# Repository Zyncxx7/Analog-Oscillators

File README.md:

# Analog-Oscillators
# Analog-Oscillators
# Analog-Oscillators

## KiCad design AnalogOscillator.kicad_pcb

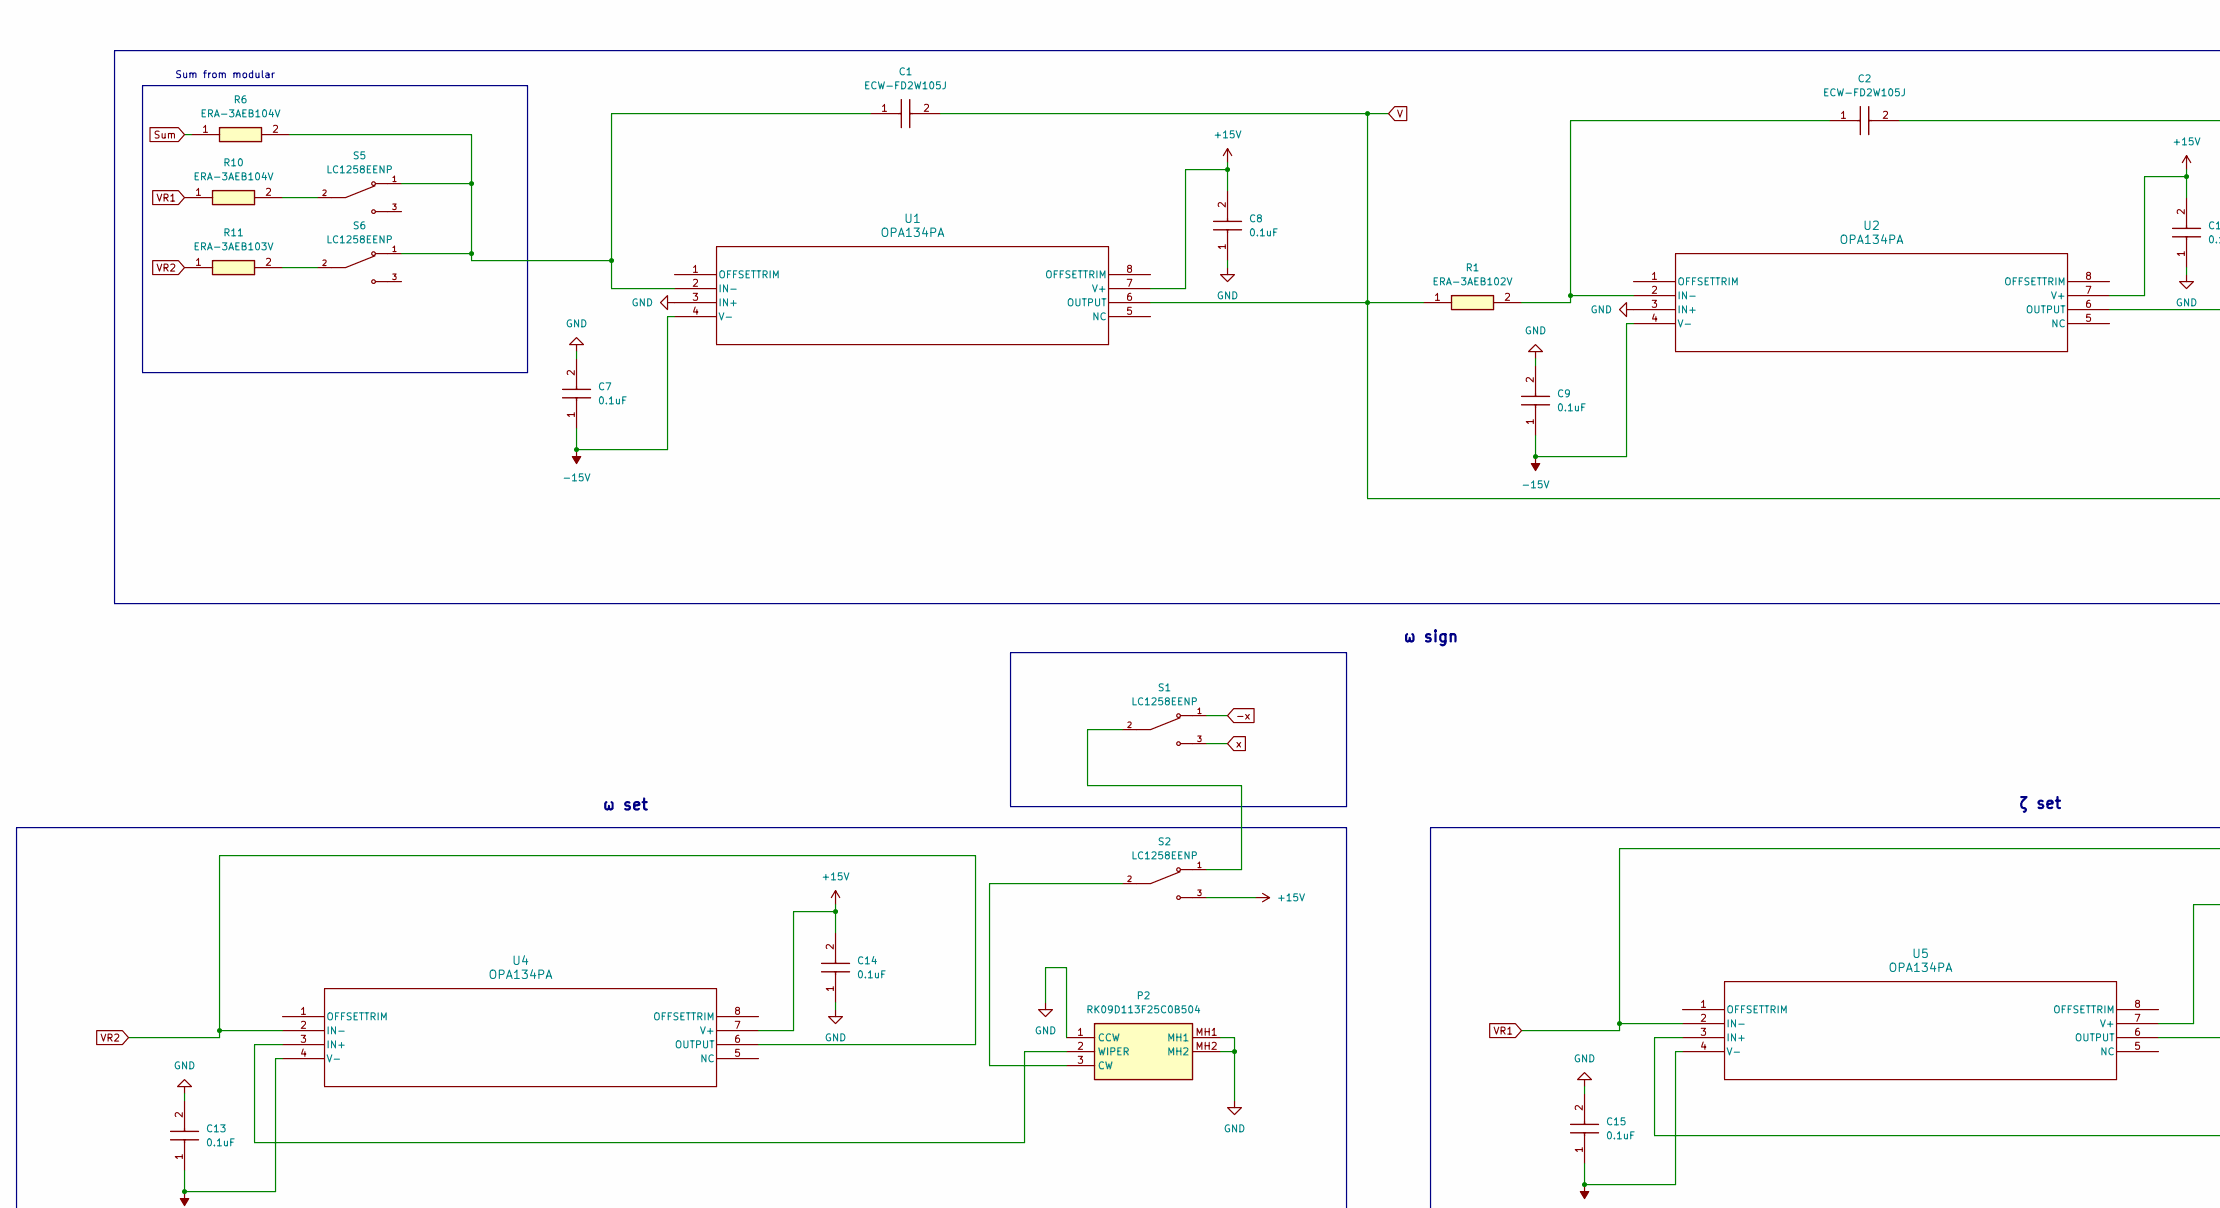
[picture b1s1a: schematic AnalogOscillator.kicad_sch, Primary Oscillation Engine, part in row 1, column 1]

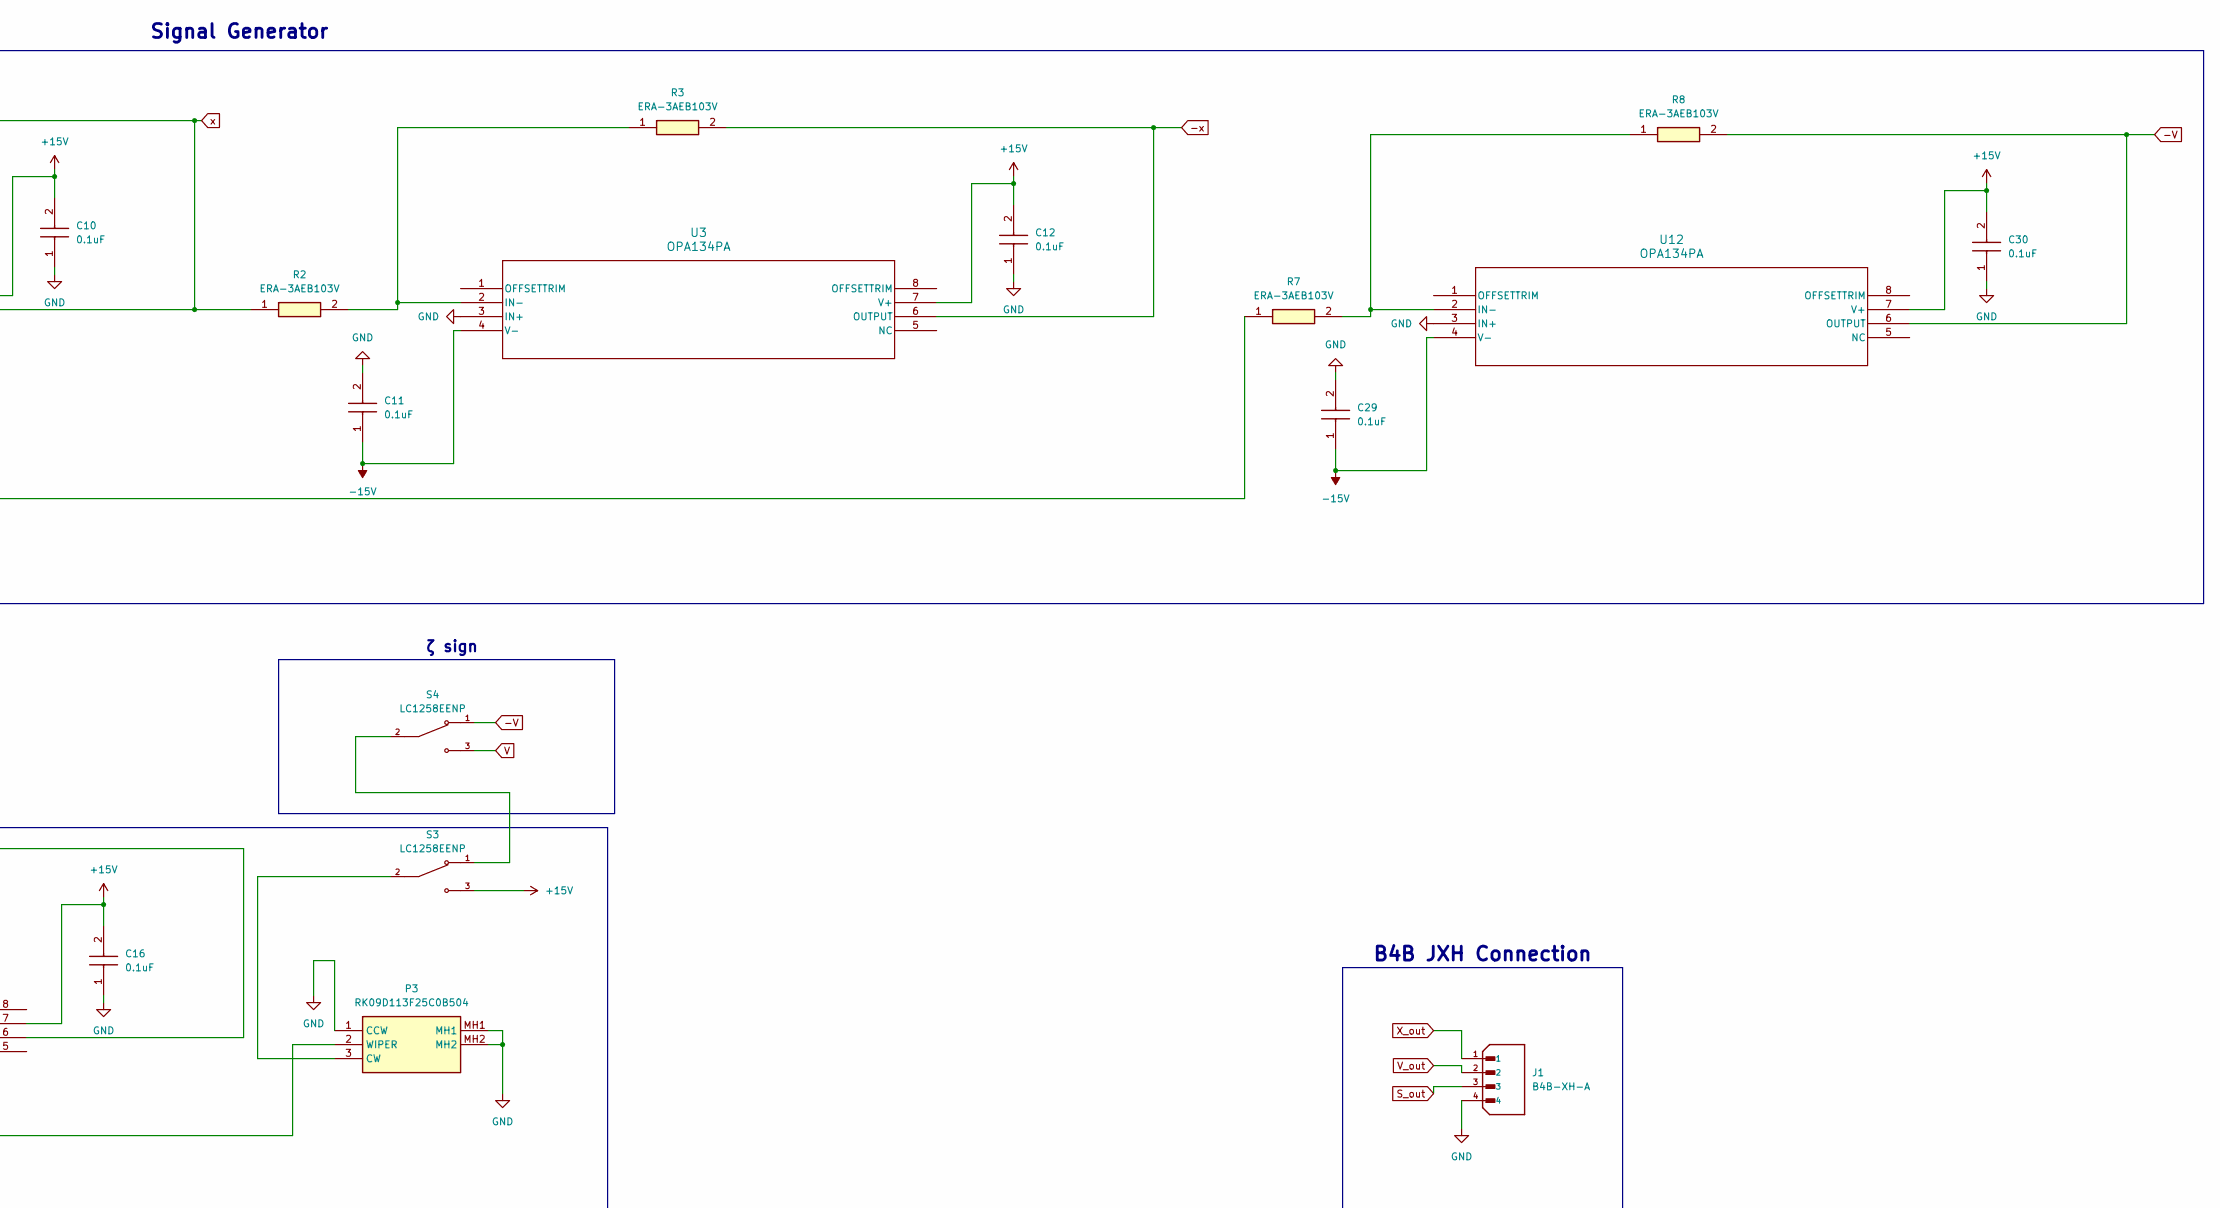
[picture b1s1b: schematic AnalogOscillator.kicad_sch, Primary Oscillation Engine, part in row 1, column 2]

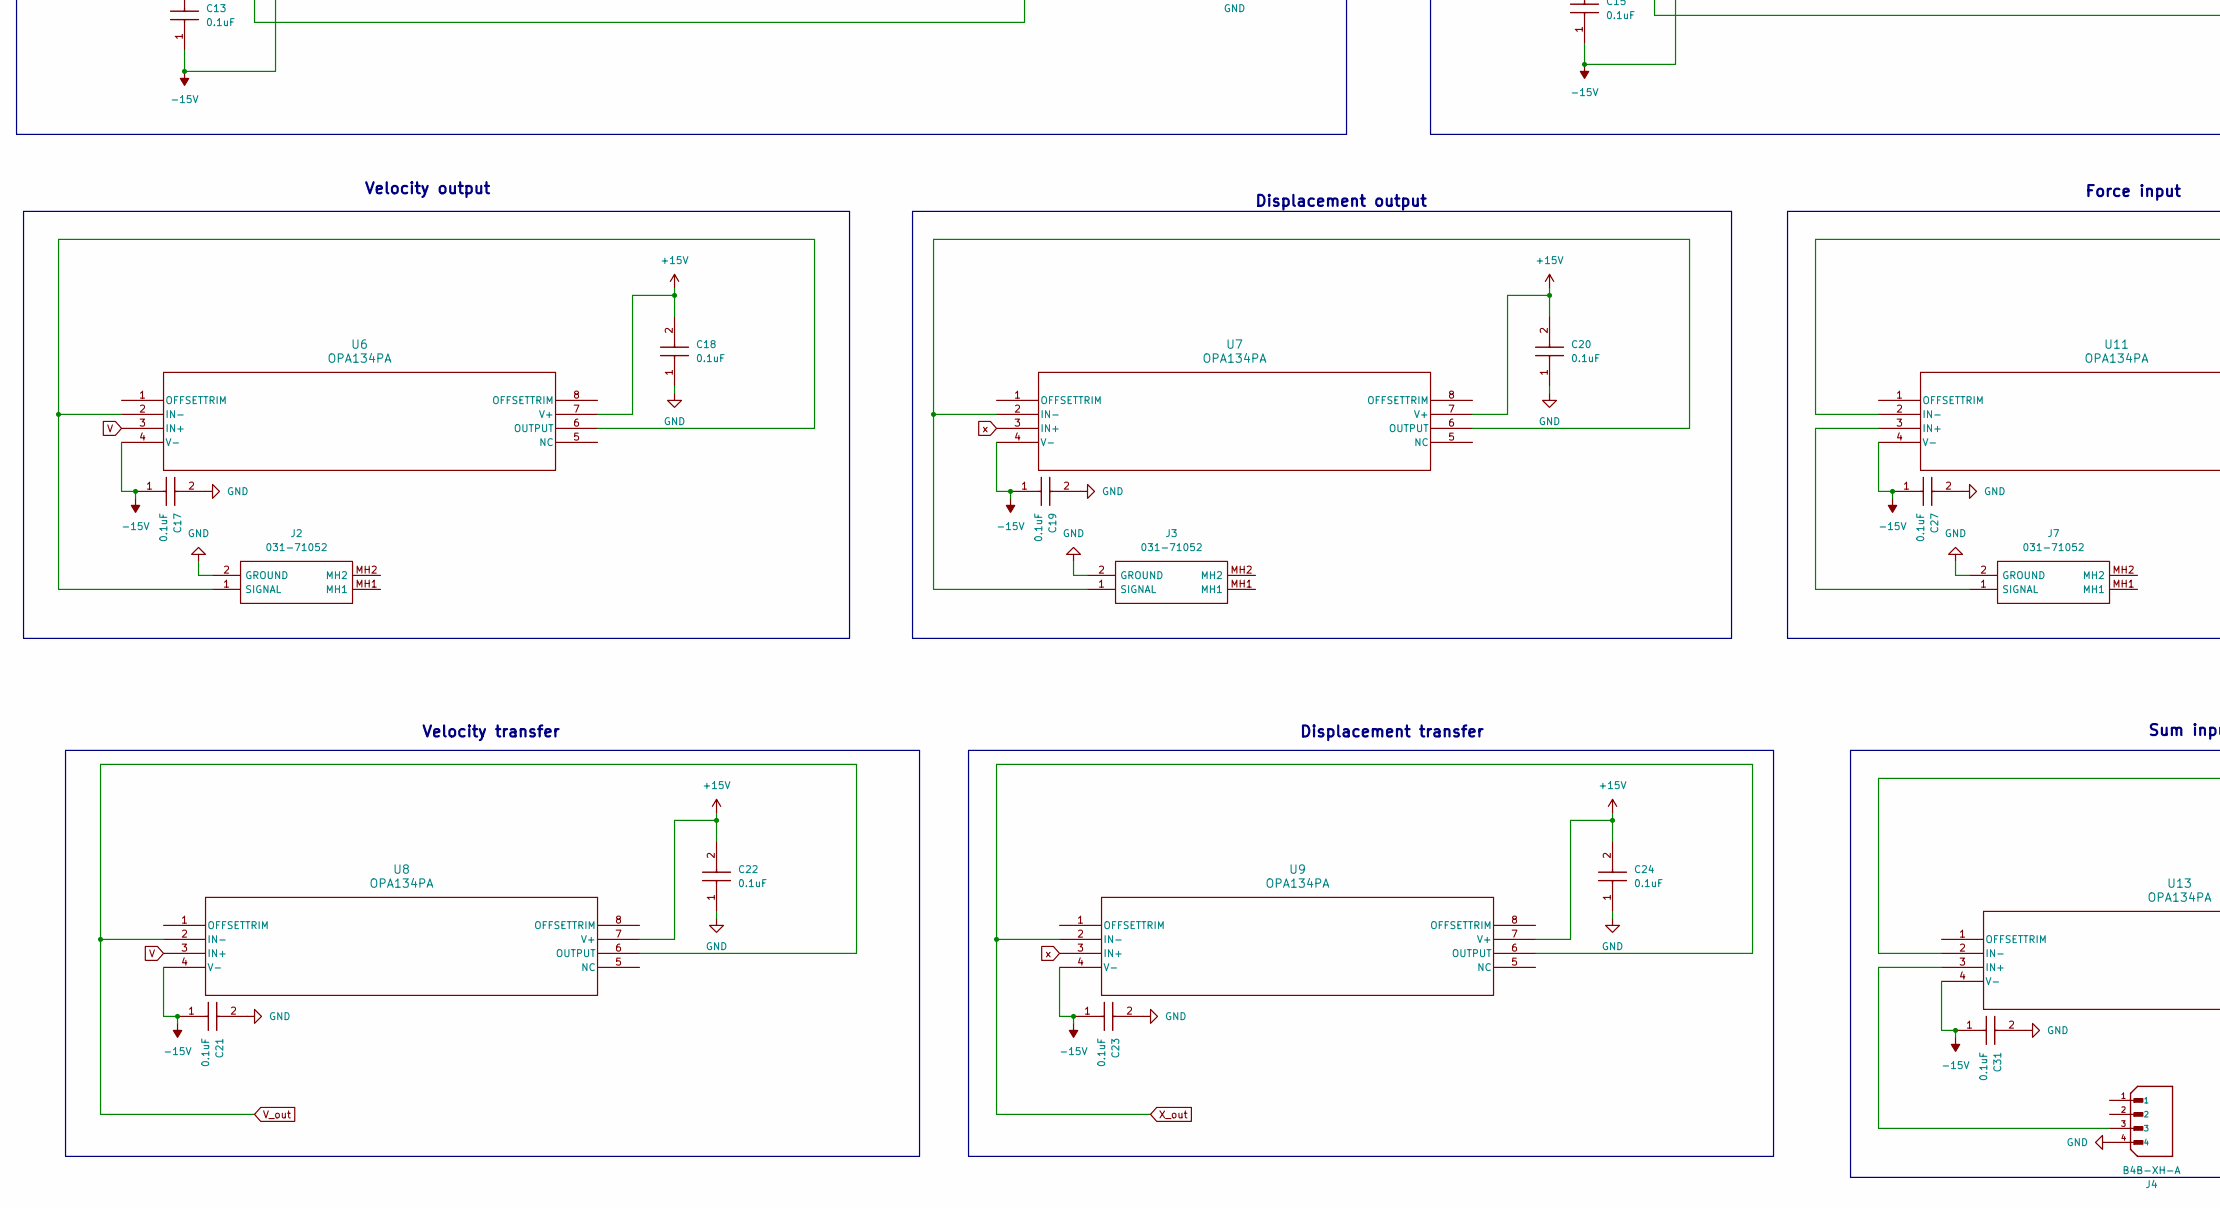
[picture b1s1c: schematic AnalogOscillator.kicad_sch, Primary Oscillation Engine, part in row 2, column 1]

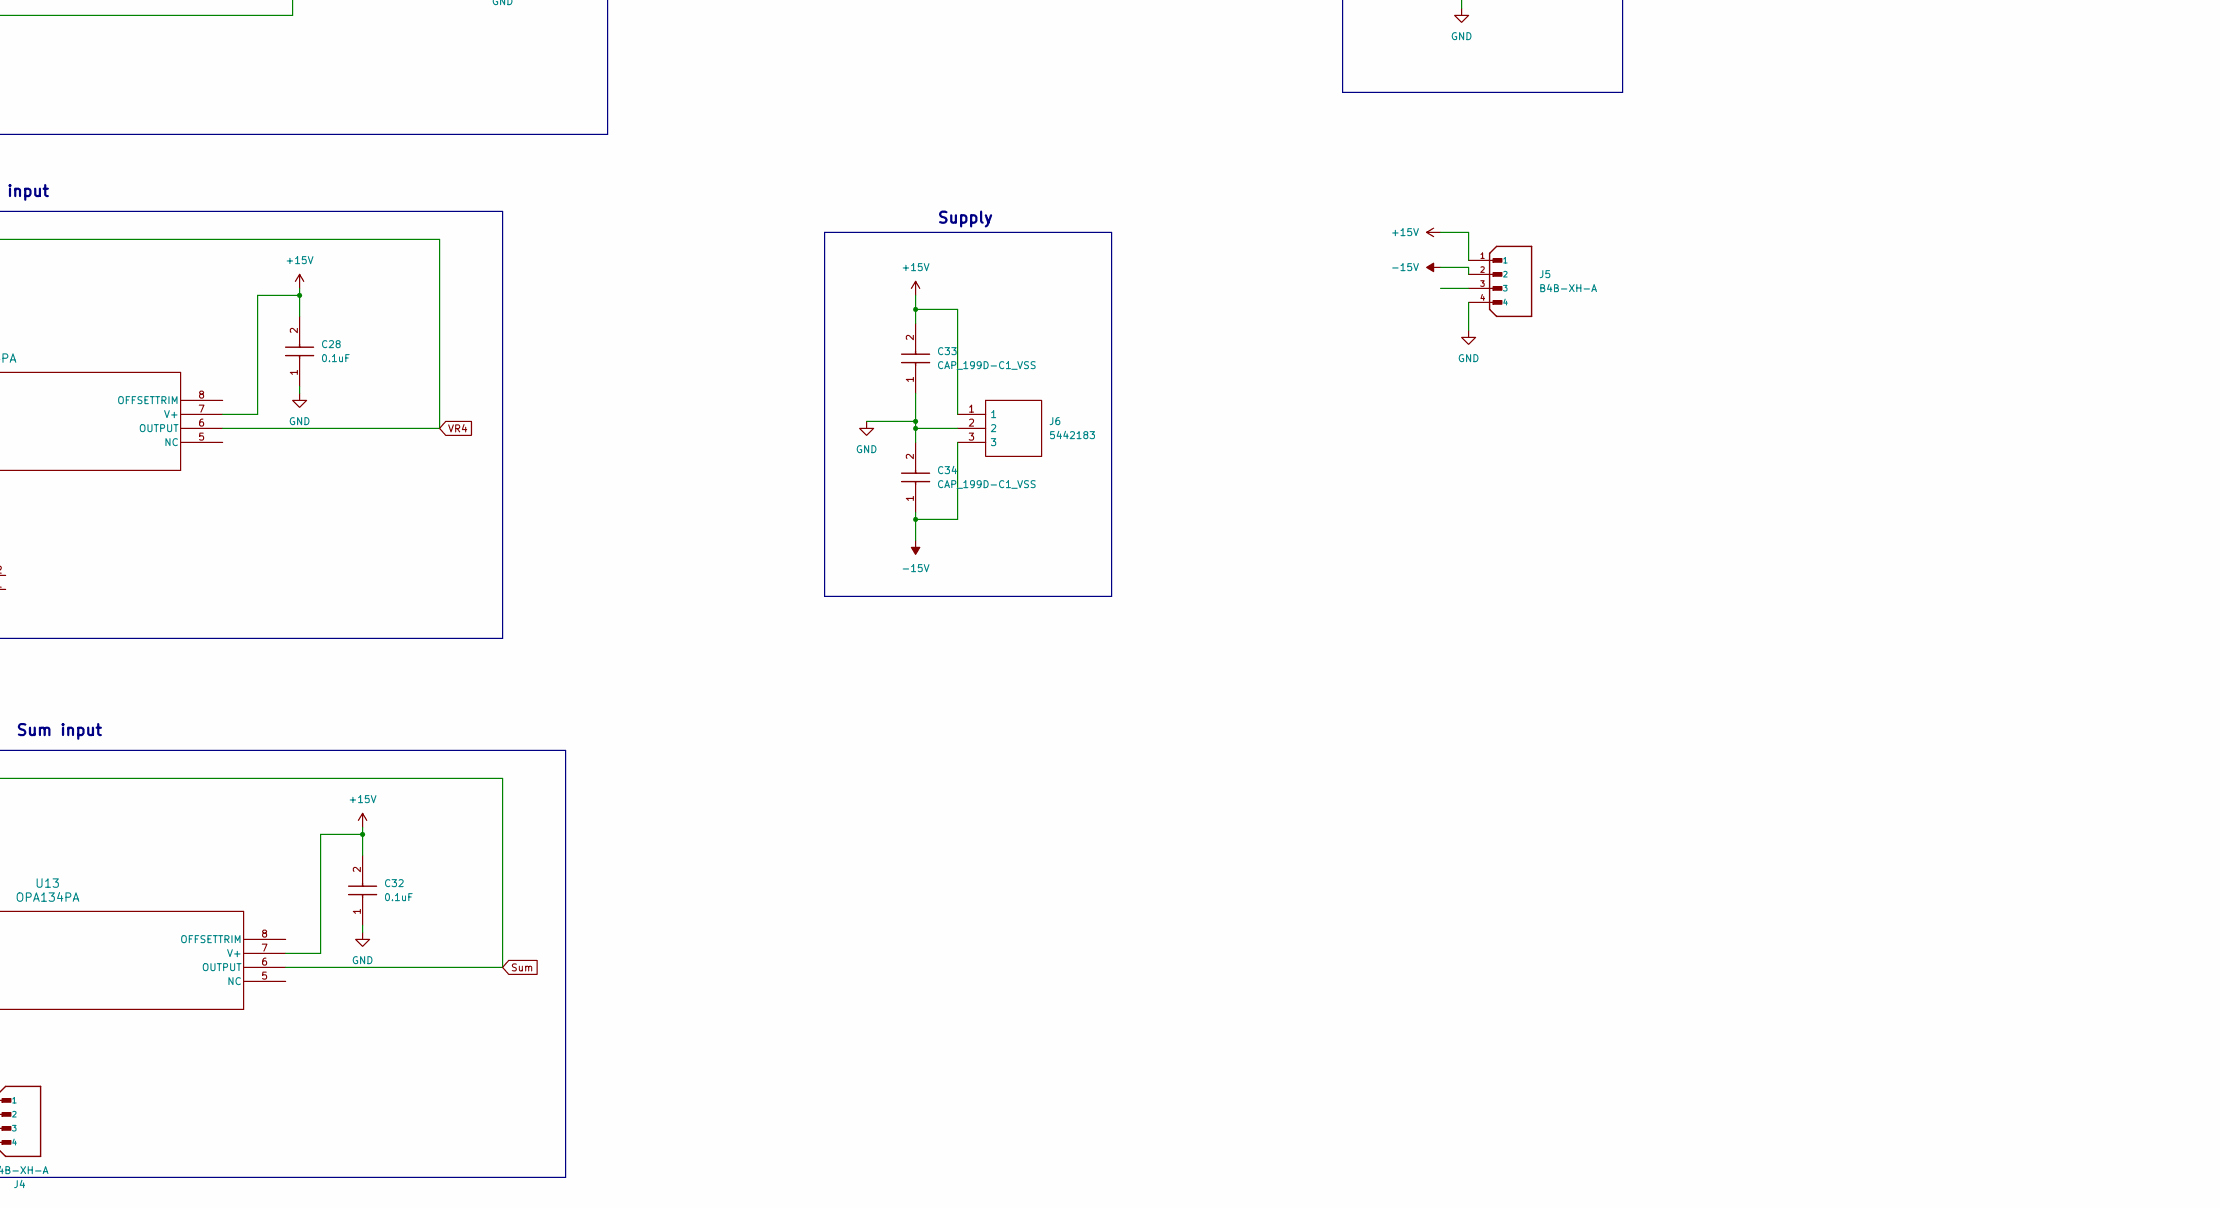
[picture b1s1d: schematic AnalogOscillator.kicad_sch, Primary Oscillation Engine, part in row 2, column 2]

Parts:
C1, C2: ECW-FD2W105J; ECWFD2W105J; Mouser Part Number 667-ECW-FD2W105J
C7, C8, C9, C10, C11, C12, C13, C14, C15, C16, C17, C18, C19, C20, C21, C22, C23, C24, C27, C28, C29, C30, C31, C32: 0.1uF; C_Rect_L13.0mm_W6.5mm_P7.50mm_P10.00mm
C33, C34: CAP_199D-C1_VSS; Mouser Part Number 187-CL21A106KQFNNNG
J1, J4, J5: B4B-XH-A; JST_B4B-XH-A; PARTREV 7/4/21
J2, J3, J7: 031-71052; 03171052; Manufacturer_Part_Number 031-71052
J6: 5442183; Mouser Part Number 651-5442183
P2, P3: RK09D113F25C0B504; Mouser Part Number 688-RK09D113F25-500K
R1: ERA-3AEB102V; ERA3AEB101V; Mouser Part Number 667-ERA-3AEB102V
R2, R3, R7, R8, R11: ERA-3AEB103V; ERA3AEB101V; Mouser Part Number 667-ERA-3AEB103V
R6, R10: ERA-3AEB104V; ERA3AEB101V; Mouser Part Number 667-ERA-3AEB104V
S1, S2, S3, S4, S5, S6: LC1258EENP; SW_LC1258EENP; PARTREV C
U1, U2, U3, U4, U5, U6, U7, U8, U9, U11, U12, U13: OPA134PA; P8

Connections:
+15V: C8.2, C10.2, C12.2, C14.2, C16.2, C18.2, C20.2, C22.2, C24.2, C28.2, C30.2, C32.2, C33.2, J5.1, J6.1, S2.3, S3.3, U1.7 (V+), U2.7 (V+), U3.7 (V+), U4.7 (V+), U5.7 (V+), U6.7 (V+), U7.7 (V+), U8.7 (V+), U9.7 (V+), U11.7 (V+), U12.7 (V+), U13.7 (V+)
-15V: C7.1, C9.1, C11.1, C13.1, C15.1, C17.1, C19.1, C21.1, C23.1, C27.1, C29.1, C31.1, C34.1, J5.2, J6.3, U1.4 (V-), U2.4 (V-), U3.4 (V-), U4.4 (V-), U5.4 (V-), U6.4 (V-), U7.4 (V-), U8.4 (V-), U9.4 (V-), U11.4 (V-), U12.4 (V-), U13.4 (V-)
-V: R8.2, S4.1, U12.6 (OUTPUT)
-x: R3.2, S1.1, U3.6 (OUTPUT)
GND: C7.2, C8.1, C9.2, C10.1, C11.2, C12.1, C13.2, C14.1, C15.2, C16.1, C17.2, C18.1, C19.2, C20.1, C21.2, C22.1, C23.2, C24.1, C27.2, C28.1, C29.2, C30.1, C31.2, C32.1, C33.1, C34.2, J1.4, J2.2 (GROUND), J3.2 (GROUND), J4.4, J5.4, J6.2, J7.2 (GROUND), P2.1 (CCW), P2.MH1, P2.MH2, P3.1 (CCW), P3.MH1, P3.MH2, U1.3 (IN+), U2.3 (IN+), U3.3 (IN+), U12.3 (IN+)
unnamed: J2.1 (SIGNAL), U6.2 (IN-), U6.6 (OUTPUT)
unnamed: J3.1 (SIGNAL), U7.2 (IN-), U7.6 (OUTPUT)
unnamed: J7.1 (SIGNAL), U11.3 (IN+)
unnamed: P2.3 (CW), S2.2
unnamed: P2.2 (WIPER), U4.3 (IN+)
unnamed: P3.3 (CW), S3.2
unnamed: P3.2 (WIPER), U5.3 (IN+)
unnamed: R10.2, S5.2
unnamed: R11.2, S6.2
unnamed: S1.2, S2.1
unnamed: S3.1, S4.2
unnamed: C1.1, R6.2, S5.1, S6.1, U1.2 (IN-)
unnamed: C2.1, R1.2, U2.2 (IN-)
unnamed: R2.2, R3.1, U3.2 (IN-)
unnamed: R7.2, R8.1, U12.2 (IN-)
unnamed: J4.3, U13.3 (IN+)
S_out: J1.3
Sum: R6.1, U13.2 (IN-), U13.6 (OUTPUT)
V: C1.2, R1.1, R7.1, S4.3, U1.6 (OUTPUT), U6.3 (IN+), U8.3 (IN+)
VR1: R10.1, U5.2 (IN-), U5.6 (OUTPUT)
VR2: R11.1, U4.2 (IN-), U4.6 (OUTPUT)
VR4: U11.2 (IN-), U11.6 (OUTPUT)
V_out: J1.2, U8.2 (IN-), U8.6 (OUTPUT)
X_out: J1.1, U9.2 (IN-), U9.6 (OUTPUT)
x: C2.2, R2.1, S1.3, U2.6 (OUTPUT), U7.3 (IN+), U9.3 (IN+)

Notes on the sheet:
ω sign
Supply
ζ sign
Sum input
Sum from modular
Signal Generator
Velocity output
Force input
ω set
Velocity transfer
Displacement output
ζ set
Displacement transfer
B4B JXH Connection

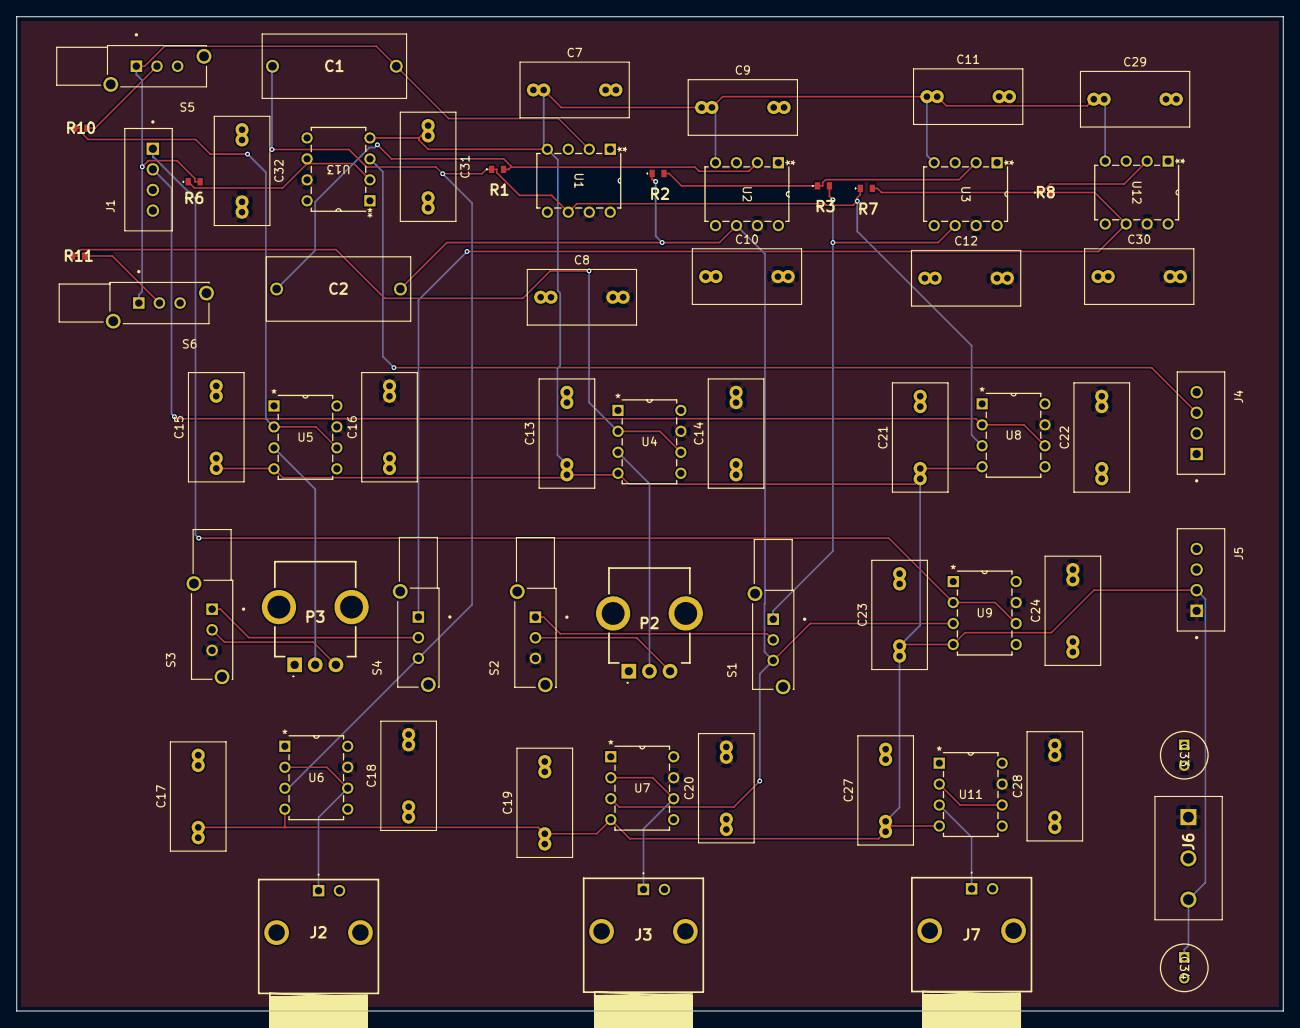
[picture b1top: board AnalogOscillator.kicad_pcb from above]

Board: 2 copper layers, 153.5 x 120.5 mm, 63 parts (0 on the bottom side), 29 nets.

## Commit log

2025-12-28 Latest KiCad file without the updated Connectors
2025-12-28 Updated connectors and SMD components
2026-01-08 "{""Full Name"":""James"",""Date of Birth"":""23/04/1985"",""Health Conditions"":""Alzheimer's, Arthritis, Dementia, Cognitive decline"",""Medications"":""Aspirin: ; Lecanemab: ; donanemab: "",""Dail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
